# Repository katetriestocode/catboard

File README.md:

# catboard

devboard following hackclub guide with 128Mb (new!) memory with rp2040 with a long cat on it, as well as mymelody and stars! 
I made this with beefy graphics projects in mind, to be able to whitstand larger graphics :) I also really wanted to have a custom devboard that suits my needs and can work for all my project prototypes!
This is it built and soldered up:

This is the back:

This is the front (but will be white!):

This is the schematic:

And this is the pcb:

|Designator|Footprint|Quantity|Value|LCSC Part #|
|---|---|---|---|---|
|"C1-C10"|0402|2|1uf|CL05A105KA5NQNC|
|"C11-C9"|0402|11|0.1uf|CL05B104KO5NNNC|
|"C13-C14"|0603|2|10uf|CL10A106KP8NNNC|
|"C15-C16"|0402|2|33pF|0402CG330J500NT|
|J1|USB_C_Receptacle_HRO_TYPE-C-31-M-12|1|USB_C_Receptacle_USB2.0_14P|TYPE-C-31-M-12|
|"R1-R2"|0402|2|5.1k|0402WGF5101TCE|
|"R3-R4"|0402|2|27|0402WGF270JTCE|
|"R5-R7"|0402|2|1K|0402WGF1001TCE|
|R6|0402|1|10k|0402WGF1002TCE|
|SW1|SW_Push_SPST_NO_Alps_SKRK|1|SW_Push|TS-1088-AR02016|
|U1|QFN-56-1EP_7x7mm_P0.4mm_EP3.2x3.2mm|1|n/a|RP2040|
|U2|SOT-23|1|MCP1700x-330xxTT|MCP1700T-3302E/TT|
|U3|WSON-8-1EP_6x5mm_P1.27mm_EP3.4x4.3mm|1|n/a|W25Q128JVP|
|Y1|Crystal_SMD_3225-4Pin_3.2x2.5mm|1|12 MHz|X322512MSB4SI|

|Item|Cost|
|---|---|
|PCBA|50.70$|
|shipping|1.50$|

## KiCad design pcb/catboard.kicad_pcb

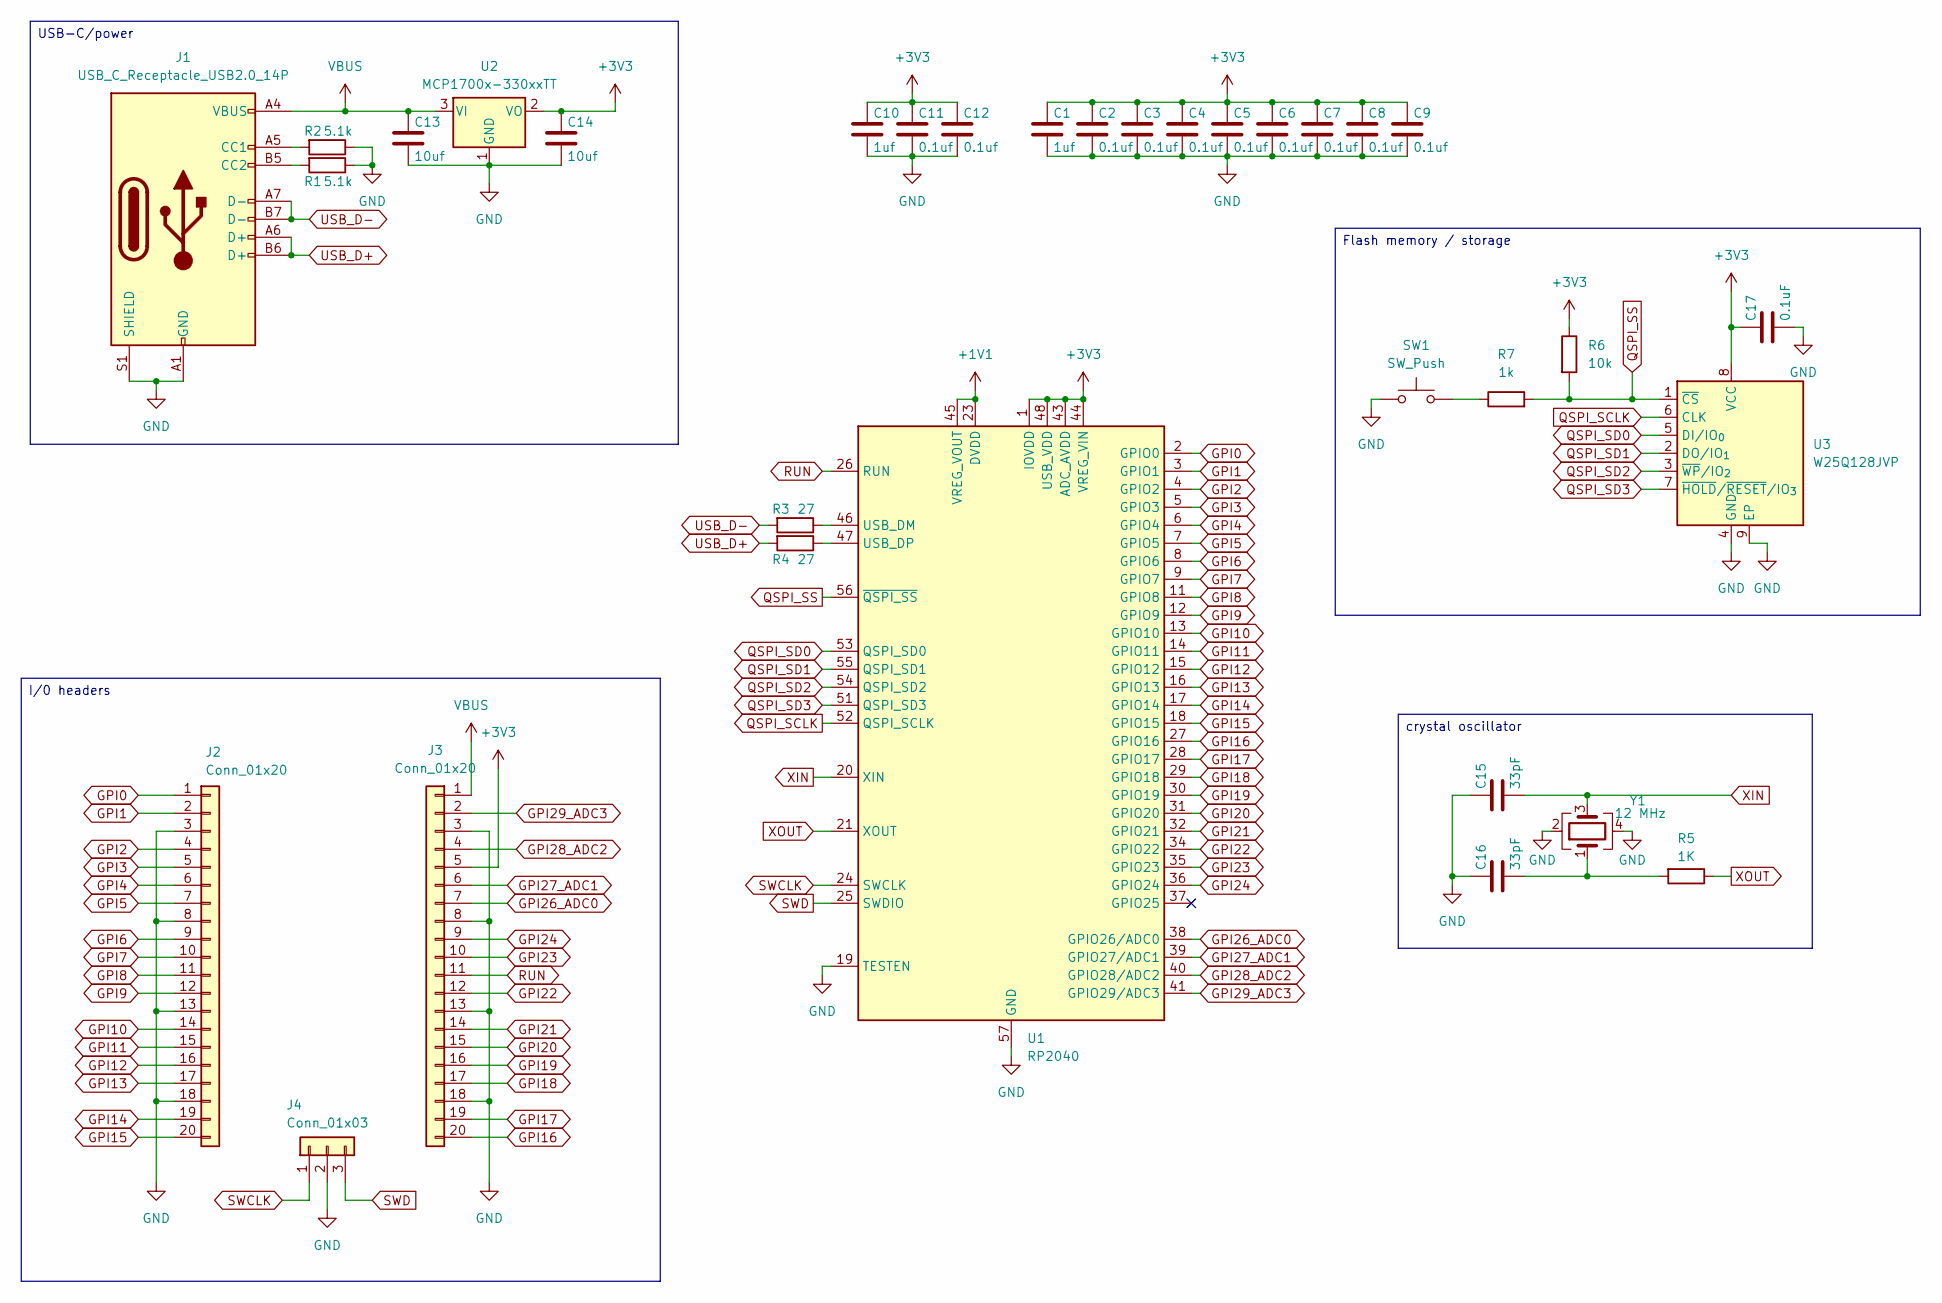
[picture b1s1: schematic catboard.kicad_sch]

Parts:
C1, C10: 1uf; C_0402_1005Metric
C2, C3, C4, C5, C6, C7, C8, C9, C11, C12: 0.1uf; C_0402_1005Metric
C13, C14: 10uf; C_0603_1608Metric
C15, C16: 33pF; C_0402_1005Metric
C17: 0.1uF; C_0402_1005Metric
J1: USB_C_Receptacle_USB2.0_14P; USB_C_Receptacle_HRO_TYPE-C-31-M-12
J2, J3: Conn_01x20; PinHeader_1x20_P2.54mm_Vertical
J4: Conn_01x03; PinHeader_1x03_P2.54mm_Vertical
R1, R2: 5.1k; R_0402_1005Metric
R3, R4: 27; R_0402_1005Metric
R5: 1K; R_0402_1005Metric
R6: 10k; R_0402_1005Metric
R7: 1k; R_0402_1005Metric
SW1: SW_Push; SW_Push_SPST_NO_Alps_SKRK
U1: RP2040; QFN-56-1EP_7x7mm_P0.4mm_EP3.2x3.2mm
U2: MCP1700x-330xxTT; SOT-23
U3: W25Q128JVP; WSON-8-1EP_6x5mm_P1.27mm_EP3.4x4.3mm
Y1: 12 MHz; Crystal_SMD_3225-4Pin_3.2x2.5mm

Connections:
+1V1: U1.23 (DVDD), U1.45 (VREG_VOUT), U1.50 (DVDD)
+3V3: C1.1, C2.1, C3.1, C4.1, C5.1, C6.1, C7.1, C8.1, C9.1, C10.1, C11.1, C12.1, C14.1, C17.1, J3.5, R6.1, U1.1 (IOVDD), U1.10 (IOVDD), U1.22 (IOVDD), U1.33 (IOVDD), U1.42 (IOVDD), U1.43 (ADC_AVDD), U1.44 (VREG_VIN), U1.48 (USB_VDD), U1.49 (IOVDD), U2.2 (VO), U3.8 (VCC)
GND: C1.2, C2.2, C3.2, C4.2, C5.2, C6.2, C7.2, C8.2, C9.2, C10.2, C11.2, C12.2, C13.2, C14.2, C15.1, C16.1, C17.2, J1.A1 (GND), J1.A12 (GND), J1.B1 (GND), J1.B12 (GND), J1.S1 (SHIELD), J2.3, J2.8, J2.13, J2.18, J3.3, J3.8, J3.13, J3.18, J4.2, R1.1, R2.1, SW1.1, U1.19 (TESTEN), U1.57 (GND), U2.1 (GND), U3.4 (GND), U3.9 (EP), Y1.2 (G), Y1.4 (G)
GPI0: J2.1, U1.2 (GPIO0)
GPI1: J2.2, U1.3 (GPIO1)
GPI2: J2.4, U1.4 (GPIO2)
GPI3: J2.5, U1.5 (GPIO3)
GPI4: J2.6, U1.6 (GPIO4)
GPI5: J2.7, U1.7 (GPIO5)
GPI6: J2.9, U1.8 (GPIO6)
GPI7: J2.10, U1.9 (GPIO7)
GPI8: J2.11, U1.11 (GPIO8)
GPI9: J2.12, U1.12 (GPIO9)
GPI10: J2.14, U1.13 (GPIO10)
GPI11: J2.15, U1.14 (GPIO11)
GPI12: J2.16, U1.15 (GPIO12)
GPI13: J2.17, U1.16 (GPIO13)
GPI14: J2.19, U1.17 (GPIO14)
GPI15: J2.20, U1.18 (GPIO15)
GPI16: J3.20, U1.27 (GPIO16)
GPI17: J3.19, U1.28 (GPIO17)
GPI18: J3.17, U1.29 (GPIO18)
GPI19: J3.16, U1.30 (GPIO19)
GPI20: J3.15, U1.31 (GPIO20)
GPI21: J3.14, U1.32 (GPIO21)
GPI22: J3.12, U1.34 (GPIO22)
GPI23: J3.10, U1.35 (GPIO23)
GPI24: J3.9, U1.36 (GPIO24)
GPI26_ADC0: J3.7, U1.38 (GPIO26/ADC0)
GPI27_ADC1: J3.6, U1.39 (GPIO27/ADC1)
GPI28_ADC2: J3.4, U1.40 (GPIO28/ADC2)
GPI29_ADC3: J3.2, U1.41 (GPIO29/ADC3)
unnamed: C16.2, R5.2, Y1.1
unnamed: J1.A5 (CC1), R2.2
unnamed: J1.B5 (CC2), R1.2
unnamed: R7.1, SW1.2
unnamed: R3.1, U1.46 (USB_DM)
unnamed: R4.1, U1.47 (USB_DP)
QSPI_SCLK: U1.52 (QSPI_SCLK), U3.6 (CLK)
QSPI_SD0: U1.53 (QSPI_SD0), U3.5 (DI/IO_{0})
QSPI_SD1: U1.55 (QSPI_SD1), U3.2 (DO/IO_{1})
QSPI_SD2: U1.54 (QSPI_SD2), U3.3 (~WP/IO_{2})
QSPI_SD3: U1.51 (QSPI_SD3), U3.7 (~HOLD/~RESET/IO_{3})
QSPI_SS: R6.2, R7.2, U1.56 (~QSPI_SS), U3.1 (~CS)
RUN: J3.11, U1.26 (RUN)
SWCLK: J4.1, U1.24 (SWCLK)
SWD: J4.3, U1.25 (SWDIO)
USB_D+: J1.A6 (D+), J1.B6 (D+), R4.2
USB_D-: J1.A7 (D-), J1.B7 (D-), R3.2
VBUS: C13.1, J1.A4 (VBUS), J1.A9 (VBUS), J1.B4 (VBUS), J1.B9 (VBUS), J3.1, U2.3 (VI)
XIN: C15.2, U1.20 (XIN), Y1.3
XOUT: R5.1, U1.21 (XOUT)

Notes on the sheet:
I/0 headers
USB-C/power
Flash memory / storage
crystal oscillator

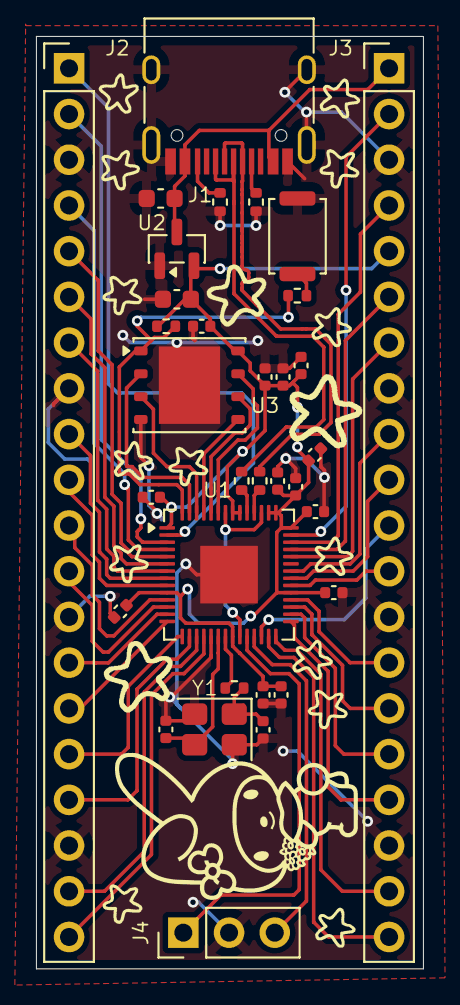
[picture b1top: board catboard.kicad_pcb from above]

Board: 2 copper layers, 21.5 x 51.8 mm, 33 parts (0 on the bottom side), 52 nets.

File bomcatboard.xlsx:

Designator | Footprint | Quantity | Value | LCSC Part #
C1, C10 | 402 | 2 | 1uf | CL05A105KA5NQNC
C11, C12, C17, C2, C3, C4, C5, C6, C7, C8, C9 | 402 | 11 | 0.1uf | CL05B104K05NNNC
C13, C14 | 603 | 2 | 10uf | CL10A106KP8NNNC
C15, C16 | 402 | 2 | 33pF | 0402CG330J500NT
J1 | USB_C_Receptacle_HRO_TYPE-C-31-M-12 | 1 | USB_C_Receptacle_USB2.0_14P | TYPE-C-31-M-12
R1, R2 | 402 | 2 | 5.1k | 0402WGF5101TCE
R3, R4 | 402 | 2 | 27 | 0402WGF270JTCE
R5, R7 | 402 | 2 | 1K | 0402WGF1001TCE
R6 | 402 | 1 | 10k | 0402WGF1002TCE
SW1 | SW_Push_SPST_NO_Alps_SKRK | 1 | SW_Push | TS-1088-AR02016
U1 | QFN-56-1EP_7x7mm_P0.4mm_EP3.2x3.2mm | 1 | RP2040 | RP2040
U2 | SOT-23 | 1 | MCP1700x-330xxTT | MCP1700T-3302E/TT
U3 | WSON-8-1EP_6x5mm_P1.27mm_EP3.4x4.3mm | 1 | W25Q128JVP | W25Q128JVP
Y1 | Crystal_SMD_3225-4Pin_3.2x2.5mm | 1 | 12 MHz | X322512MSB4SI
total price PCBA: 50.70$
shipping: 1.5$

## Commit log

2026-05-03 boop
2026-05-03 badeep
2026-05-03 beep
2026-05-04 badoop
2026-05-07 bbbbb
2026-05-07 Update README with BOM file location
    Added note about BOM file location in README.
2026-05-08 boooop
2026-05-08 media update
2026-05-08 readmeeee
2026-05-08 get ready for trouble make it double
2026-05-14 Add BOM table to README
    Added a Bill of Materials (BOM) table to the README.
2026-05-14 Add blinky
2026-05-14 bom update
2026-05-14 fix?
2026-05-14 fix again
2026-05-18 star
2026-06-30 added built img
